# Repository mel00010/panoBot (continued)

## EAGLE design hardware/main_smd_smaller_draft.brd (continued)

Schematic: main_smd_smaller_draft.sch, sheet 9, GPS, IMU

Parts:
C3, C75: 10nF; 0603
C4, C5, C7: 0.1uF; 0402
C6: 10uF; 0603
C74: 1.0uF; 0402
IC1: S1315F8_RAW; S1315F8_SMT
J5: 73100-0114
U4: LSM9DS1; PQFN24P43_350X300X102L35X23N

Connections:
3.3V: C5.1, C6.1, C7.1, C74.1, C75.1, IC1.5 (VBAT), IC1.11 (VCC33), U4.1 (VDDIO), U4.3 (VDDIO), U4.22 (VDD), U4.23 (VDD); also elsewhere on the board
ANTENNA_GND: IC1.2 (AGND), IC1.3 (AGND), IC1.4 (AGND), IC1.26 (AGND), IC1.28 (AGND), IC1.29 (AGND), IC1.33 (AGND), IC1.35 (AGND), IC1.36 (AGND), J5.2 (GND), J5.3 (GND), J5.4 (GND), J5.5 (GND)
ANTENNA_IN: IC1.1 (RFIN), J5.1 (RF)
GND: C3.2, C4.2, C5.2, C6.2, C7.2, C74.2, C75.2, IC1.6 (GND), IC1.9 (GND), IC1.10 (GND), IC1.12 (GND), IC1.15 (GND), IC1.17 (GND), IC1.19 (GND), IC1.21 (GND), IC1.22 (GND), IC1.23 (GND), IC1.24 (GND), U4.14 (RES), U4.15 (RES), U4.16 (RES), U4.17 (RES), U4.18 (RES), U4.19 (GND), U4.20 (GND); also elsewhere on the board
unnamed: C4.1, U4.24 (C1)
unnamed: C3.1, U4.21 (CAP)
SPI3_MISO: U4.5 (SDO_A/G), U4.6 (SDO_M); also elsewhere on the board
SPI3_MOSI: U4.4 (SDA/SDI/SDO); also elsewhere on the board
SPI3_NSS1: U4.8 (CS_M); also elsewhere on the board
SPI3_NSS2: U4.7 (CS_A/G); also elsewhere on the board
SPI3_SCK: U4.2 (SCL/SPC); also elsewhere on the board
USART1_RX: IC1.30 (TXD0); also elsewhere on the board
USART1_TX: IC1.31 (RXD0); also elsewhere on the board

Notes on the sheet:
GPS
IMU

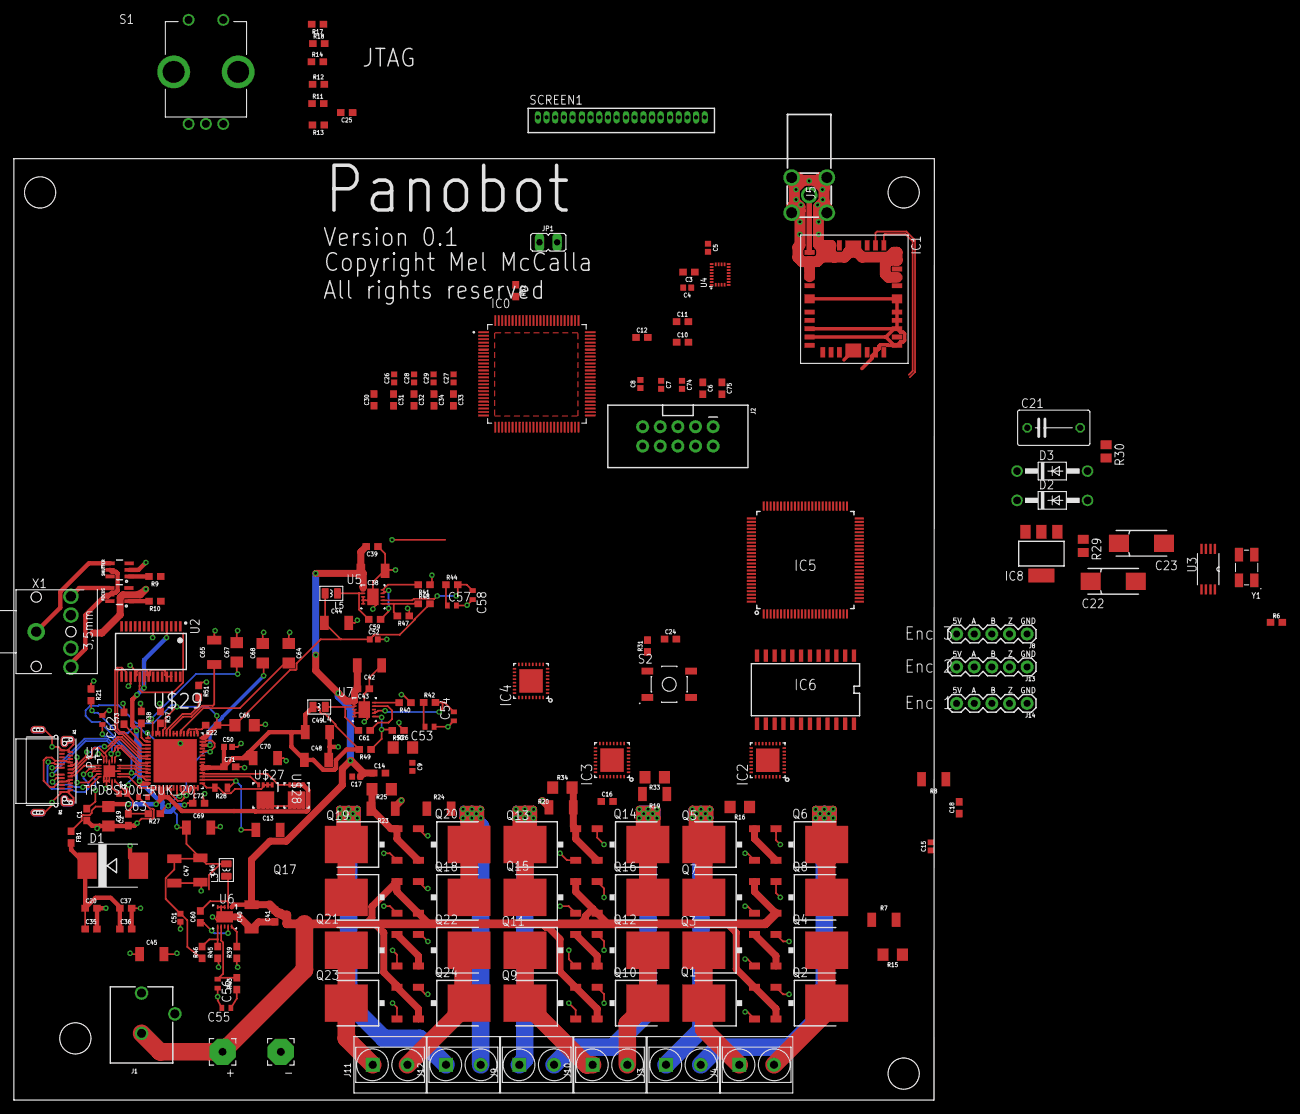
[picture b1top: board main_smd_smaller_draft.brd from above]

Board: 4 copper layers, 132.7 x 135.7 mm, 192 parts (0 on the bottom side), 180 nets.

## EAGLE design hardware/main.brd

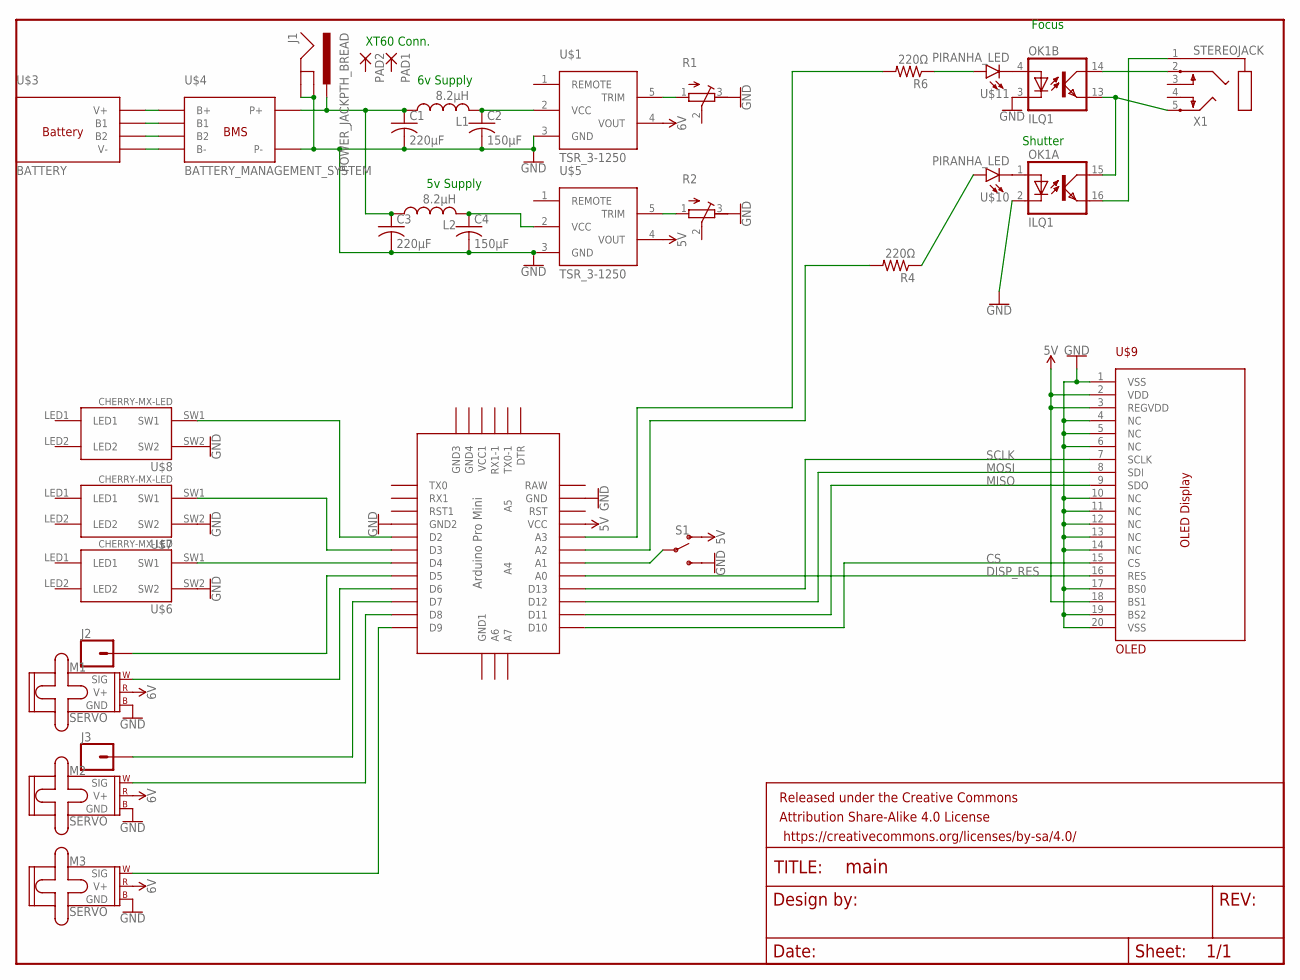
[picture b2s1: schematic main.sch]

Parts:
C1, C3: 220µF; C075-032X103
C2, C4: 150µF; C075-032X103
FRAME1: FRAME-LETTER; CREATIVE_COMMONS
J1: POWER_JACKPTH_BREAD; POWER_JACK_PTH_BREAD
J2, J3: CONN_01; 1X01
L1, L2: 8.2µH; IRF-1
M1, M2, M3: SERVO; 1X03
OK1: ILQ1; DIL16
PAD1, PAD2: 3,81/1,1
R1, R2: R-TRIMM64W; RTRIM64W
R4, R6: 220Ω; 0207/10
S1: SWITCH-SPDT-PTH-11.6X4.0MM; SWITCH_SPDT_PTH_11.6X4.0MM
U$1, U$5: TSR_3-1250; SIP-5
U$2: ABK-PRO-MINI
U$6, U$7, U$8: CHERRY-MX-LED
U$9: OLED; SIP-20
U$10, U$11: PIRANHA_LED; LED_PIRANHA_5MM
X1: STEREOJACK; STX3100

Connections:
5V: S1.1 (O), U$2.VCC, U$5.4 (VOUT), U$9.2 (VDD), U$9.3 (REGVDD), U$9.18 (BS1)
6V: M1.2 (V+), M2.2 (V+), M3.2 (V+), U$1.4 (VOUT)
BUTTON_1: U$2.D2, U$8.SW1
BUTTON_2: U$2.D3, U$7.SW1
BUTTON_3: U$2.D4, U$6.SW1
CS: U$2.D10, U$9.15 (CS)
DISP_RES: U$2.A0, U$9.16 (RES)
FOCUS: R6.2, U$2.A3
GND: C1.2, C2.2, C3.2, C4.2, J1.GND, J1.GNDBREAK, M1.3 (GND), M2.3 (GND), M3.3 (GND), OK1.2 (C), OK1.3 (C), R1.3 (E), R2.3 (E), S1.3 (S), U$1.3 (GND), U$2.GND, U$2.GND1 (GND2), U$5.3 (GND), U$6.SW2, U$7.SW2, U$8.SW2, U$9.1 (VSS), U$9.4 (NC), U$9.5 (NC), U$9.6 (NC), U$9.10 (NC), U$9.11 (NC), U$9.12 (NC), U$9.13 (NC), U$9.14 (NC), U$9.17 (BS0), U$9.19 (BS2), U$9.20 (VSS)
MISO: U$2.D11, U$9.9 (SDO)
MODE_SWITCH: S1.2, U$2.A1
MOSI: U$2.D12, U$9.8 (SDI)
unnamed: OK1.14 (COL), X1.2
unnamed: OK1.16 (EMIT), X1.1
unnamed: OK1.4 (A), U$11.+@0 (C), U$11.+@1 (C)
unnamed: C2.1, L1.2, U$1.2 (VCC)
unnamed: R1.1 (A), U$1.5 (TRIM)
unnamed: C4.1, L2.2, U$5.2 (VCC)
unnamed: R2.1 (A), U$5.5 (TRIM)
unnamed: R6.1, U$11.-@0 (A), U$11.-@1 (A)
unnamed: R4.1, U$10.-@0 (A), U$10.-@1 (A)
unnamed: OK1.1 (A), U$10.+@0 (C), U$10.+@1 (C)
unnamed: OK1.13 (EMIT), OK1.15 (COL), X1.5
P+: C1.1, C3.1, J1.PWR, L1.1, L2.1
SCLK: U$2.D13, U$9.7 (SCLK)
SERVO_1_CONTROL: M1.1 (SIG), U$2.D6
SERVO_1_FEEDBACK: J2.1, U$2.D5
SERVO_2_CONTROL: M2.1 (SIG), U$2.D8
SERVO_2_FEEDBACK: J3.1, U$2.D7
SERVO_3_CONTROL: M3.1 (SIG), U$2.D9
SHUTTER: R4.2, U$2.A2

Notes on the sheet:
XT60 Conn.
5v Supply
6v Supply
Shutter
Focus

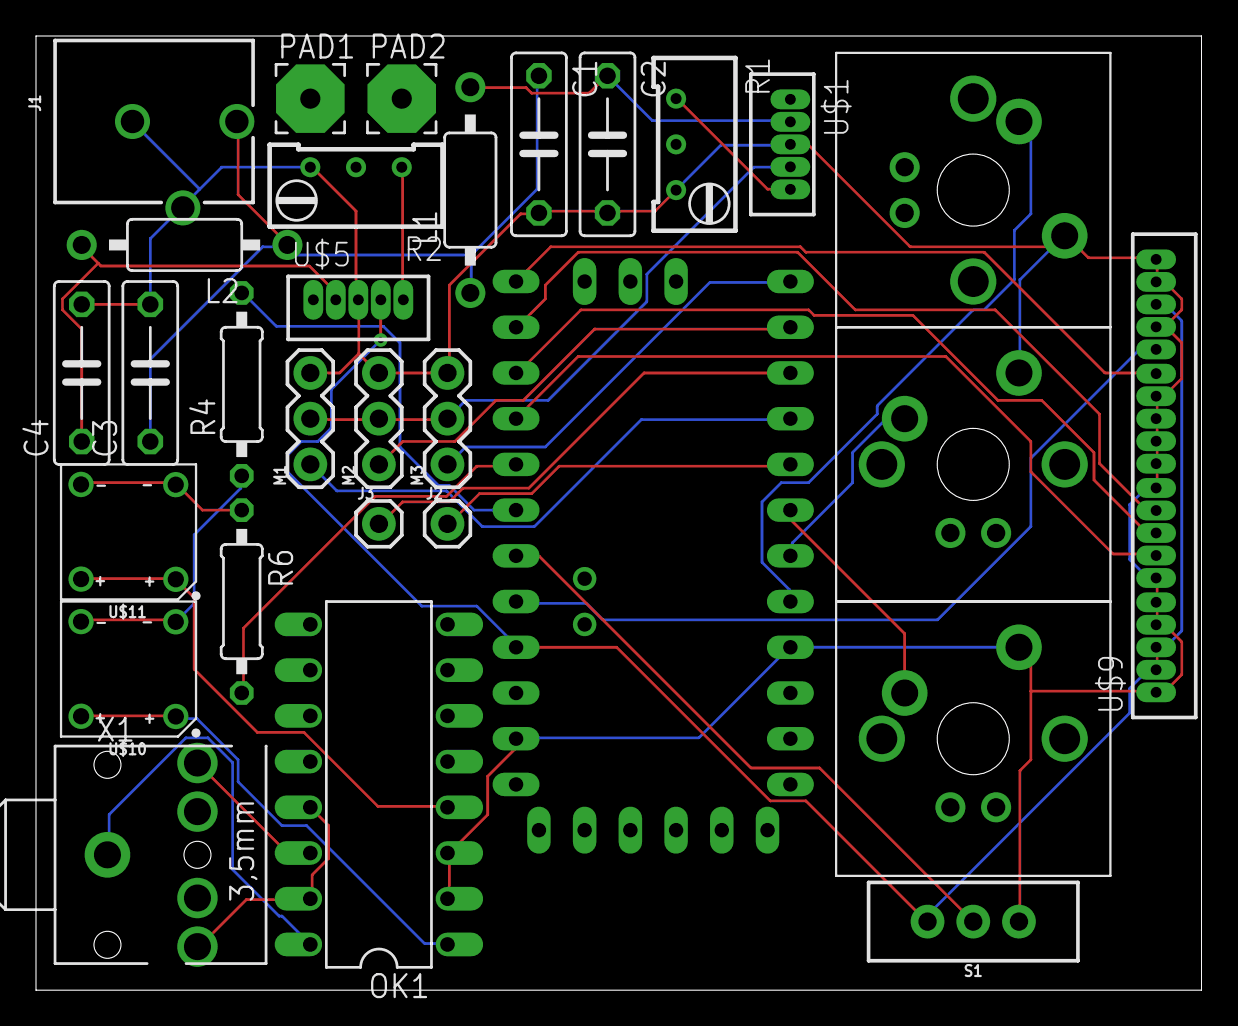
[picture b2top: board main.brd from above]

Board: 2 copper layers, 64.8 x 53.0 mm, 31 parts (0 on the bottom side), 31 nets.

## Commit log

2018-02-08 Updated .gitignore
2018-02-13 Added cmake and eagle files
2018-02-13 Updated hardware/.gitignore
2018-02-14 Set up build system to work properly with avr-gcc
2018-02-14 Added protobuf requirement to src/GUI/CMakeLists.txt
2018-02-20 Rough template of main window
2018-02-21 Updated CMakeLists.txt to fix baud rate for arduino
2018-02-22 Updated arduino core to the latest version
2018-02-22 Updated hardware files for eagle
2018-02-22 No longer using Arduino Core library
    For some reason, binaries linked with the Arduino Core library refuse to
    run. For this reason, this project will be using raw AVR C.
2018-02-22 Added Setup library
2018-02-22 Updated Eclipse project files
2018-02-22 Updated cmake/avr-arduino-toolchain.cmake
2018-02-22 Added example blink program in panoBot.cpp using avr c
2018-03-07 Adding screen files
2018-03-07 adding my name to the readme
2018-03-07 adding some example code for the screen from the documentation
2018-03-09 Adding example code from datasheet, as well as the datasheet itself to the screen directory. Will need to be changed to be functional with AVR C.
2018-03-09 PIDLoop almost done
2018-03-11 updated servo code
2018-03-11 updated button code, and pid loop to recieve servo control
2018-03-13 Renamed screen directory to Display
2018-03-13 Added Util folder
2018-03-13 Removed separate files for setting up pins and setting up serial
2018-03-13 Added Connection folder
2018-03-13 Added Camera folder
2018-03-13 Added Buttons folder
2018-03-13 Refactored directory structure
2018-03-13 Updated Eclipse files
2018-03-13 Updated hardware
2018-03-13 Updated files in cmake directory
2018-03-13 Updated Display directory
2018-03-13 Added utility functions
    Added delay.cpp
    Added delay.hpp
    Added delete.cpp
    Added delete.hpp
    Added new.cpp
    Added new.hpp
2018-03-13 Updated Setup
2018-03-13 Updated camera code to use new delay functions
2018-03-13 Updated display interface
2018-03-13 Updated main()
2018-03-13 Updated Display code so it compiles
2018-03-13 Updated README.md with updates on project progress
2018-03-13 added a few binary command calls
2018-03-13 Updated PID loop
2018-03-14 Updated cmake build system to fix reset loop bug
2018-03-14 Display is now working
2018-03-14 Added an empty .gdbinit for the debugger
2018-03-14 testing servo running
2018-03-14 typo in registers
2018-03-14 Added display loop and some comments
2018-03-14 Updated servo code for testing
2018-03-14 test another servo
2018-03-14 Updated servotest and display
2018-03-14 Updated delay functions in delay.cpp to be macros.
2018-03-14 Fine tuned timings for writing to the display
2018-03-14 Getting going on some display functions
2018-03-14 Changes to functions for display
2018-03-14 Added missing semicolon and formatted Display.cpp
2018-03-14 Servos now work. Updated servo code.
2018-03-15 Display changes
2018-03-15 Some changes by Ben
2018-03-17 updated readme with members main responsibilities
2018-04-02 Moved cmake folder into new git project and added submodule
2018-04-02 Updated hardware/eagle.epf
2018-04-03 removed an accidentally uploaded file
2018-04-13 Cleaned up schematic and board layout
2018-04-13 Updated common cmake repo
2018-04-13 Updated Eclipse settings file
2018-04-18 Updated Eagle project files
2018-04-18 Added missing function declaration in Servo.hpp
2018-04-18 Added CMake build system to GUI sub-project
2018-05-30 Finished SMD board layout for hardware
2018-09-24 Updated hardware directory and other misc updates
